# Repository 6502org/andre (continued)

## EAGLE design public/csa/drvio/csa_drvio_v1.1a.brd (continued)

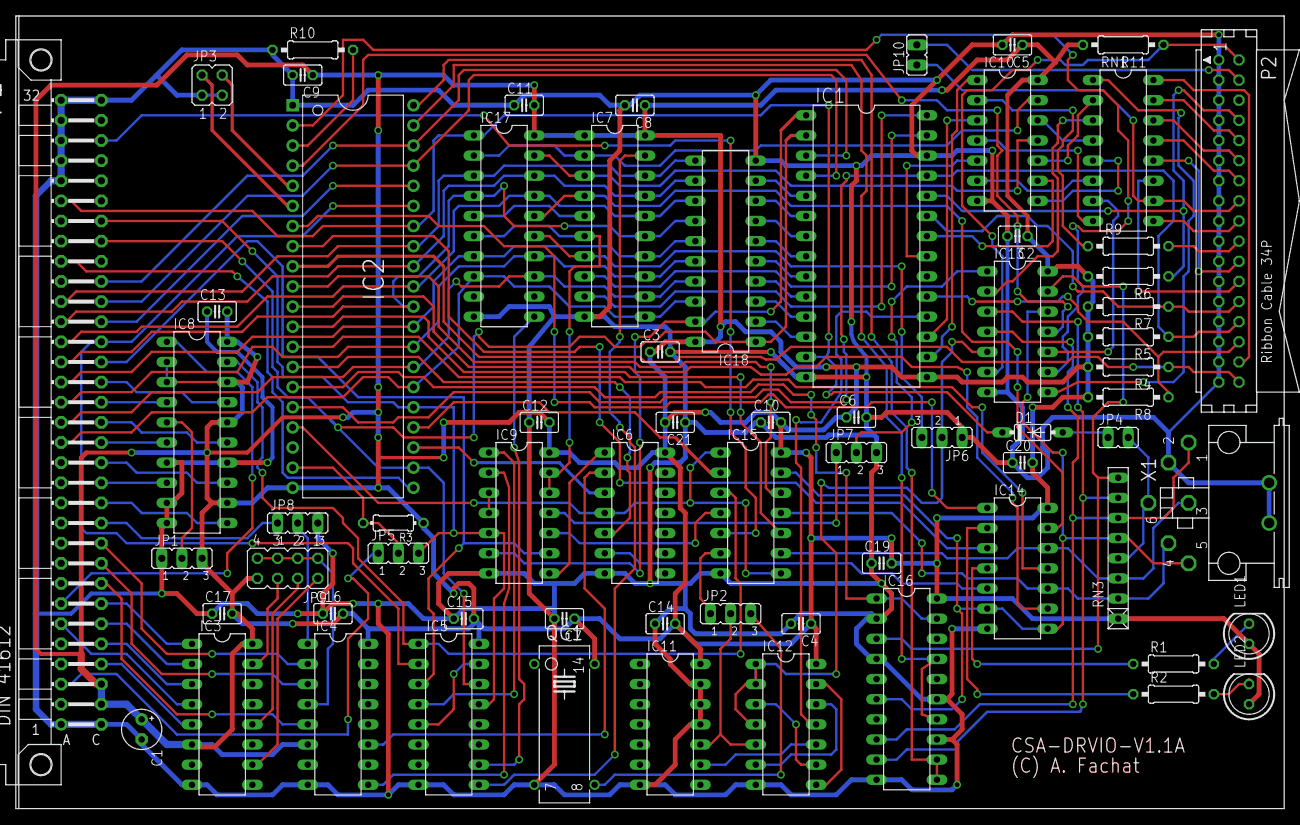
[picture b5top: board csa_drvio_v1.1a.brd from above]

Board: 2 copper layers, 160.0 x 100.0 mm, 68 parts (0 on the bottom side), 143 nets.

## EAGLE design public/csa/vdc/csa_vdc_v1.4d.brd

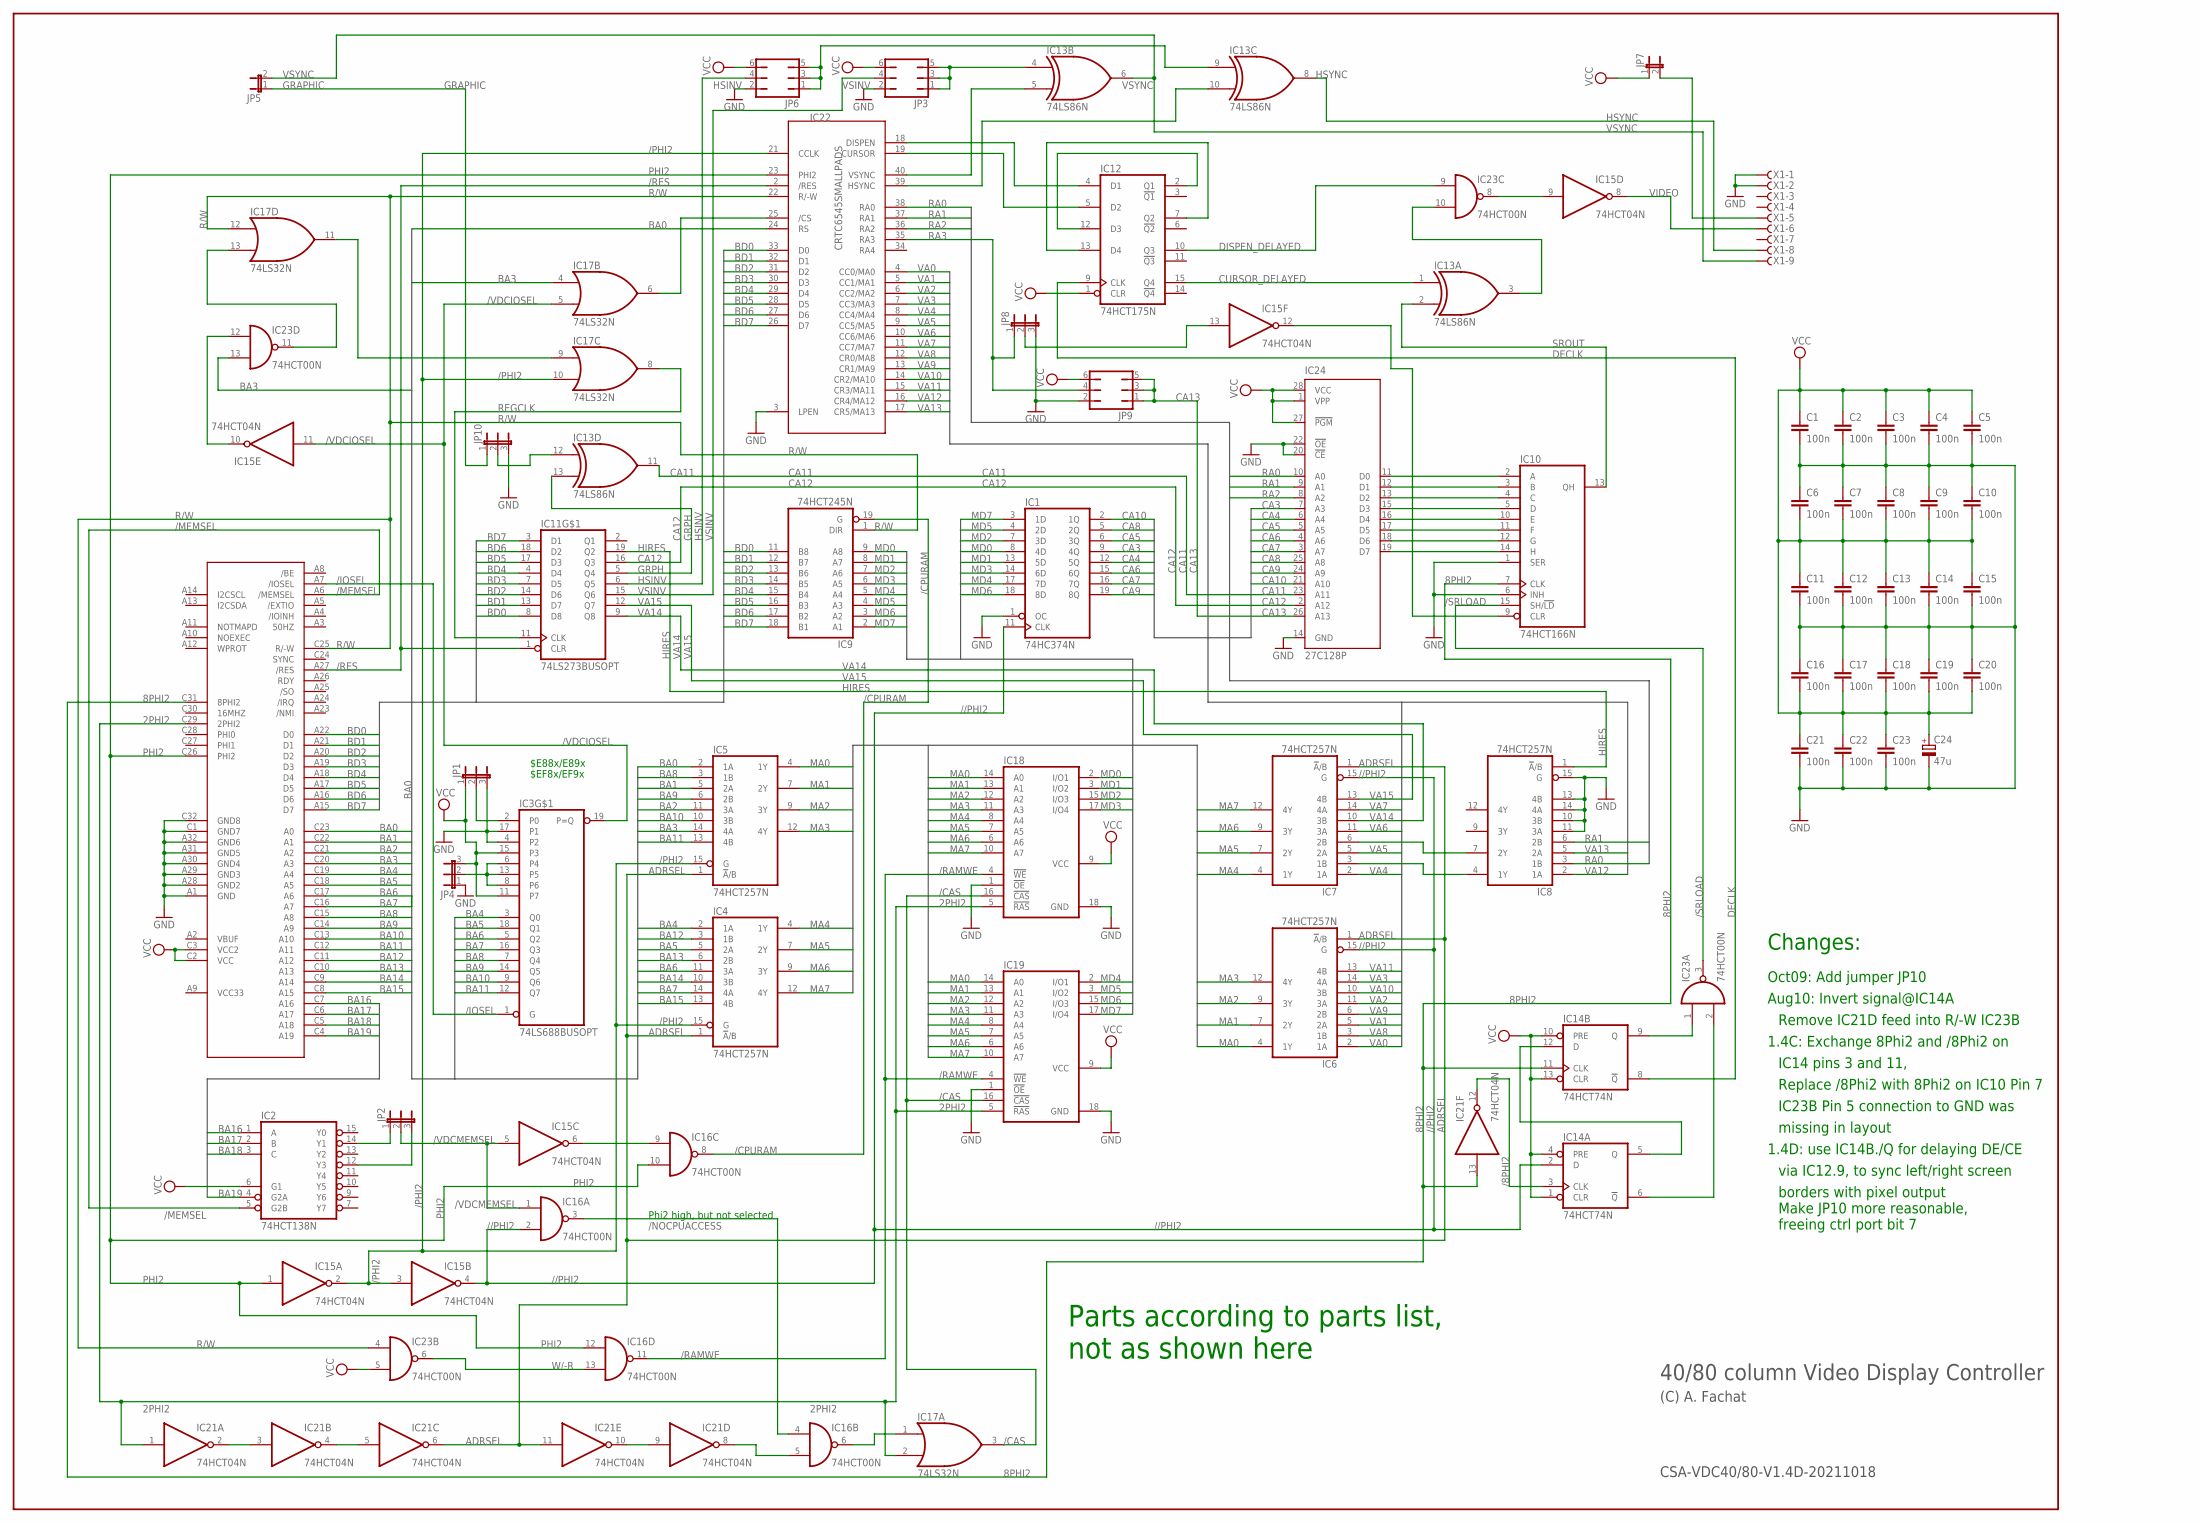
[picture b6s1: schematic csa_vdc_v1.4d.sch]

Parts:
C1, C2, C3, C4, C5, C6, C7, C8, C9, C10, C11, C12, C13, C14, C15, C16, C17, C18, C19, C20, C21, C22, C23: 100n; C025-025X050
C24: 47u; E2,5-5
IC1: 74HC374N; DIL20
IC2: 74HCT138N; DIL16
IC3: 74LS688BUSOPT; DIL20
IC4, IC5, IC6, IC7, IC8: 74HCT257N; DIL16
IC9: 74HCT245N; DIL20
IC10: 74HCT166N; DIL16
IC11: 74LS273BUSOPT; DIL20
IC12: 74HCT175N; DIL16
IC13: 74LS86N; DIL14
IC14: 74HCT74N; DIL14
IC15, IC21: 74HCT04N; DIL14
IC16, IC23: 74HCT00N; DIL14
IC17: 74LS32N; DIL14
IC18, IC19: 41464C; DIL18
IC22: CRTC6545SMALLPADS; DIP40
IC24: 27C128P; DIL28-6
JP1, JP2, JP4, JP8, JP10: JP2E; JP2
JP3, JP6, JP9: JP3Q
JP5, JP7: JP1E; JP1
U$1: CSABUS
X1: F09HPS; F09HP

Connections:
2PHI2: IC17.2 (I1), IC18.5 (!RAS), IC19.5 (!RAS), IC21.1 (I), U$1.C29 (2PHI2)
8PHI2: IC10.7 (CLK), IC14.11 (CLK), IC21.13 (I), U$1.C31 (8PHI2)
/8PHI2: IC14.3 (CLK), IC21.12 (O)
//PHI2: IC1.11 (CLK), IC6.15 (G), IC7.15 (G), IC14.2 (D), IC15.4 (O), IC16.2 (I1)
/CAS: IC17.3 (O), IC18.16 (!CAS), IC19.16 (!CAS)
/CPURAM: IC9.19 (G), IC16.8 (O)
/IOSEL: IC3.1 (G), U$1.A7 (/IOSEL)
/MEMSEL: IC2.5 (G2B), U$1.A6 (/MEMSEL)
/NOCPUACCESS: IC16.3 (O), IC16.4 (I0)
/PHI2: IC4.15 (G), IC5.15 (G), IC15.2 (O), IC15.3 (I), IC17.10 (I1), IC22.21 (CCLK)
/RAMWE: IC16.11 (O), IC18.4 (!WE), IC19.4 (!WE)
/RES: IC11.1 (CLR), IC22.2 (/RES), U$1.A27 (/RES)
/SRLOAD: IC10.15 (SH/!LD), IC23.3 (O)
/VDCIOSEL: IC3.19 (P=Q), IC15.11 (I), IC17.5 (I1)
/VDCMEMSEL: IC15.5 (I), IC16.1 (I0), JP2.2
ADRSEL: IC4.1 (!A!/B), IC5.1 (!A!/B), IC6.1 (!A!/B), IC7.1 (!A!/B), IC21.6 (O), IC21.11 (I)
BA0: IC5.2 (1A), IC22.24 (RS), U$1.C23 (A0)
BA1: IC5.5 (2A), U$1.C22 (A1)
BA2: IC5.11 (3A), U$1.C21 (A2)
BA3: IC5.14 (4A), IC17.4 (I0), IC23.13 (I1), U$1.C20 (A3)
BA4: IC3.3 (Q0), IC4.2 (1A), U$1.C19 (A4)
BA5: IC3.18 (Q1), IC4.5 (2A), U$1.C18 (A5)
BA6: IC3.5 (Q2), IC4.11 (3A), U$1.C17 (A6)
BA7: IC3.16 (Q3), IC4.14 (4A), U$1.C16 (A7)
BA8: IC3.7 (Q4), IC5.3 (1B), U$1.C15 (A8)
BA9: IC3.14 (Q5), IC5.6 (2B), U$1.C14 (A9)
BA10: IC3.9 (Q6), IC5.10 (3B), U$1.C13 (A10)
BA11: IC3.12 (Q7), IC5.13 (4B), U$1.C12 (A11)
BA12: IC4.3 (1B), U$1.C11 (A12)
BA13: IC4.6 (2B), U$1.C10 (A13)
BA14: IC4.10 (3B), U$1.C9 (A14)
BA15: IC4.13 (4B), U$1.C8 (A15)
BA16: IC2.1 (A), U$1.C7 (A16)
BA17: IC2.2 (B), U$1.C6 (A17)
BA18: IC2.3 (C), U$1.C5 (A18)
BA19: IC2.4 (G2A), U$1.C4 (A19)
BD0: IC9.11 (B8), IC11.8 (D8), IC22.33 (D0), U$1.A22 (D0)
BD1: IC9.12 (B7), IC11.13 (D7), IC22.32 (D1), U$1.A21 (D1)
BD2: IC9.13 (B6), IC11.14 (D6), IC22.31 (D2), U$1.A20 (D2)
BD3: IC9.14 (B5), IC11.7 (D5), IC22.30 (D3), U$1.A19 (D3)
BD4: IC9.15 (B4), IC11.4 (D4), IC22.29 (D4), U$1.A18 (D4)
BD5: IC9.16 (B3), IC11.17 (D3), IC22.28 (D5), U$1.A17 (D5)
BD6: IC9.17 (B2), IC11.18 (D2), IC22.27 (D6), U$1.A16 (D6)
BD7: IC9.18 (B1), IC11.3 (D1), IC22.26 (D7), U$1.A15 (D7)
CA3: IC1.9 (4Q), IC24.7 (A3)
CA4: IC1.12 (5Q), IC24.6 (A4)
CA5: IC1.6 (3Q), IC24.5 (A5)
CA6: IC1.15 (6Q), IC24.4 (A6)
CA7: IC1.16 (7Q), IC24.3 (A7)
CA8: IC1.5 (2Q), IC24.25 (A8)
CA9: IC1.19 (8Q), IC24.24 (A9)
CA10: IC1.2 (1Q), IC24.21 (A10)
CA11: IC13.11 (O), IC24.23 (A11)
CA12: IC11.16 (Q3), IC24.2 (A12)
CA13: IC24.26 (A13), JP9.1, JP9.3, JP9.5
CURSOR_DELAYED: IC12.15 (Q4), IC13.1 (I0)
DECLK: IC12.9 (CLK), IC14.8 (!Q)
DISPEN_DELAYED: IC12.10 (Q3), IC23.9 (I0)
GND: C1.2, C2.2, C3.2, C4.2, C5.2, C6.1, C7.1, C8.1, C9.1, C10.1, C11.2, C12.2, C13.2, C14.2, C15.2, C16.1, C17.1, C18.1, C19.1, C20.1, C21.2, C22.2, C23.2, C24.-, IC1.1 (OC), IC1.10 (GND), IC2.8 (GND), IC3.4 (P2), IC3.10 (GND), IC3.17 (P1), IC4.8 (GND), IC5.8 (GND), IC6.8 (GND), IC7.8 (GND), IC8.8 (GND), IC8.10 (3B), IC8.11 (3A), IC8.13 (4B), IC8.14 (4A), IC8.15 (G), IC9.10 (GND), IC10.1 (SER), IC10.6 (INH), IC10.8 (GND), IC11.10 (GND), IC12.8 (GND), IC13.7 (GND), IC14.7 (GND), IC15.7 (GND), IC16.7 (GND), IC17.7 (GND), IC18.1 (!OE), IC18.18 (GND), IC19.1 (!OE), IC19.18 (GND), IC21.7 (GND), IC22.1 (GND), IC22.3 (LPEN), IC23.7 (GND), IC24.14 (GND), IC24.20 (!CE), IC24.22 (!OE), JP1.3, JP3.2, JP4.1, JP6.2, JP8.3, JP9.2, JP10.3, U$1.A1 (GND), U$1.A28 (GND2), U$1.A29 (GND3), U$1.A30 (GND4), U$1.A31 (GND5), U$1.A32 (GND6), U$1.C1 (GND7), U$1.C32 (GND8), X1.1, X1.2
GRAPHIC: JP5.1, JP10.1
GRPH: IC11.5 (Q4), IC13.13 (I1)
HIRES: IC8.1 (!A!/B), IC11.19 (Q2)
HSINV: IC11.6 (Q5), JP6.4
HSYNC: IC13.8 (O), X1.8
MA0: IC5.4 (1Y), IC6.4 (1Y), IC18.14 (A0), IC19.14 (A0)
MA1: IC5.7 (2Y), IC6.7 (2Y), IC18.13 (A1), IC19.13 (A1)
MA2: IC5.9 (3Y), IC6.9 (3Y), IC18.12 (A2), IC19.12 (A2)
MA3: IC5.12 (4Y), IC6.12 (4Y), IC18.11 (A3), IC19.11 (A3)
MA4: IC4.4 (1Y), IC7.4 (1Y), IC18.8 (A4), IC19.8 (A4)
MA5: IC4.7 (2Y), IC7.7 (2Y), IC18.7 (A5), IC19.7 (A5)
MA6: IC4.9 (3Y), IC7.9 (3Y), IC18.6 (A6), IC19.6 (A6)
MA7: IC4.12 (4Y), IC7.12 (4Y), IC18.10 (A7), IC19.10 (A7)
MD0: IC1.8 (4D), IC9.9 (A8), IC18.2 (I/O1)
MD1: IC1.13 (5D), IC9.8 (A7), IC18.3 (I/O2)
MD2: IC1.7 (3D), IC9.7 (A6), IC18.15 (I/O3)
MD3: IC1.14 (6D), IC9.6 (A5), IC18.17 (I/O4)
MD4: IC1.17 (7D), IC9.5 (A4), IC19.2 (I/O1)
MD5: IC1.4 (2D), IC9.4 (A3), IC19.3 (I/O2)
MD6: IC1.18 (8D), IC9.3 (A2), IC19.15 (I/O3)
MD7: IC1.3 (1D), IC9.2 (A1), IC19.17 (I/O4)
unnamed: IC7.3 (1B), IC8.4 (1Y)
unnamed: IC3.2 (P0), JP1.2
unnamed: IC7.6 (2B), IC8.7 (2Y)
unnamed: IC10.2 (A), IC24.11 (D0)
unnamed: IC10.3 (B), IC24.12 (D1)
unnamed: IC10.4 (C), IC24.13 (D2)
unnamed: IC10.5 (D), IC24.15 (D3)
unnamed: IC10.10 (E), IC24.16 (D4)
unnamed: IC10.11 (F), IC24.17 (D5)
unnamed: IC10.12 (G), IC24.18 (D6)
unnamed: IC10.14 (H), IC24.19 (D7)
unnamed: IC2.14 (Y1), JP2.1
unnamed: IC2.12 (Y3), JP2.3
unnamed: IC14.6 (!Q), IC23.2 (I1)
unnamed: IC12.4 (D1), IC22.18 (DISPEN)
unnamed: IC3.6 (P4), IC3.8 (P6), IC3.13 (P5), JP4.2
unnamed: IC21.2 (O), IC21.3 (I)
unnamed: IC21.4 (O), IC21.5 (I)
unnamed: IC12.5 (D2), IC22.19 (CURSOR)
unnamed: IC21.9 (I), IC21.10 (O)
unnamed: IC13.9 (I0), JP6.1, JP6.3, JP6.5
unnamed: IC16.5 (I1), IC21.8 (O)
unnamed: IC16.6 (O), IC17.1 (I0)
unnamed: IC17.13 (I1), IC23.11 (O)
unnamed: IC15.6 (O), IC16.9 (I0)
unnamed: IC12.2 (Q1), IC12.12 (D3)
unnamed: IC12.7 (Q2), IC12.13 (D4)
unnamed: IC13.4 (I0), JP3.1, JP3.3, JP3.5
unnamed: IC10.9 (CLR), IC15.12 (O)
unnamed: IC13.3 (O), IC23.10 (I1)
unnamed: JP7.2, X1.5
unnamed: IC15.9 (I), IC23.8 (O)
unnamed: IC14.5 (Q), IC14.12 (D)
unnamed: IC13.5 (I1), IC22.40 (VSYNC)
unnamed: IC15.13 (I), JP8.2
unnamed: IC14.9 (Q), IC23.1 (I0)
unnamed: IC13.10 (I1), IC22.39 (HSYNC)
unnamed: IC13.12 (I0), JP10.2
unnamed: IC17.6 (O), IC22.25 (/CS)
unnamed: IC15.10 (O), IC23.12 (I0)
unnamed: IC17.9 (I0), IC17.11 (O)
PHI2: IC15.1 (I), IC16.10 (I1), IC16.12 (I0), IC22.23 (PHI2), U$1.C26 (PHI2)
R/W: IC9.1 (DIR), IC17.12 (I0), IC22.22 (R/-W), IC23.4 (I0), U$1.C25 (R/-W)
RA0: IC8.3 (1B), IC22.38 (RA0), IC24.10 (A0)
RA1: IC8.6 (2B), IC22.37 (RA1), IC24.9 (A1)
RA2: IC22.36 (RA2), IC24.8 (A2)
RA3: IC22.35 (RA3), JP8.1, JP9.4
REGCLK: IC11.11 (CLK), IC17.8 (O)
SROUT: IC10.13 (QH), IC13.2 (I1)
VA0: IC6.2 (1A), IC22.4 (CC0/MA0)
VA1: IC6.5 (2A), IC22.5 (CC1/MA1)
VA2: IC6.11 (3A), IC22.6 (CC2/MA2)
VA3: IC6.14 (4A), IC22.7 (CC3/MA3)
VA4: IC7.2 (1A), IC22.8 (CC4/MA4)
VA5: IC7.5 (2A), IC22.9 (CC5/MA5)
VA6: IC7.11 (3A), IC22.10 (CC6/MA6)
VA7: IC7.14 (4A), IC22.11 (CC7/MA7)
VA8: IC6.3 (1B), IC22.12 (CR0/MA8)
VA9: IC6.6 (2B), IC22.13 (CR1/MA9)
VA10: IC6.10 (3B), IC22.14 (CR2/MA10)
VA11: IC6.13 (4B), IC22.15 (CR3/MA11)
VA12: IC8.2 (1A), IC22.16 (CR4/MA12)
VA13: IC8.5 (2A), IC22.17 (CR5/MA13)
VA14: IC7.10 (3B), IC11.9 (Q8)
VA15: IC7.13 (4B), IC11.12 (Q7)
VCC: C1.1, C2.1, C3.1, C4.1, C5.1, C6.2, C7.2, C8.2, C9.2, C10.2, C11.1, C12.1, C13.1, C14.1, C15.1, C16.2, C17.2, C18.2, C19.2, C20.2, C21.1, C22.1, C23.1, C24.+, IC1.20 (VCC), IC2.6 (G1), IC2.16 (VCC), IC3.11 (P7), IC3.15 (P3), IC3.20 (VCC), IC4.16 (VCC), IC5.16 (VCC), IC6.16 (VCC), IC7.16 (VCC), IC8.16 (VCC), IC9.20 (VCC), IC10.16 (VCC), IC11.20 (VCC), IC12.1 (CLR), IC12.16 (VCC), IC13.14 (VCC), IC14.1 (CLR), IC14.4 (PRE), IC14.10 (PRE), IC14.13 (CLR), IC14.14 (VCC), IC15.14 (VCC), IC16.14 (VCC), IC17.14 (VCC), IC18.9 (VCC), IC19.9 (VCC), IC21.14 (VCC), IC22.20 (VCC), IC23.5 (I1), IC23.14 (VCC), IC24.1 (VPP), IC24.27 (!PGM), IC24.28 (VCC), JP1.1, JP3.6, JP4.3, JP6.6, JP7.1, JP9.6, U$1.C2 (VCC), U$1.C3 (VCC2)
VIDEO: IC15.8 (O), X1.6
VSINV: IC11.15 (Q6), JP3.4
VSYNC: IC13.6 (O), JP5.2, X1.9
W/-R: IC16.13 (I1), IC23.6 (O)

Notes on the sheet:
40/80 column Video Display Controller
CSA-VDC40/80-V1.4D-20211018
(C) A. Fachat
Phi2 high, but not selected
$E88x/E89x
$EF8x/EF9x
Parts according to parts list,
not as shown here
Changes:
Oct09: Add jumper JP10
Aug10: Invert signal@IC14A
Remove IC21D feed into R/-W IC23B
1.4C: Exchange 8Phi2 and /8Phi2 on
Replace /8Phi2 with 8Phi2 on IC10 Pin 7
IC14 pins 3 and 11,
IC23B Pin 5 connection to GND was
missing in layout
1.4D: use IC14B./Q for delaying DE/CE
via IC12.9, to sync left/right screen
borders with pixel output
Make JP10 more reasonable, freeing ctrl port bit 7

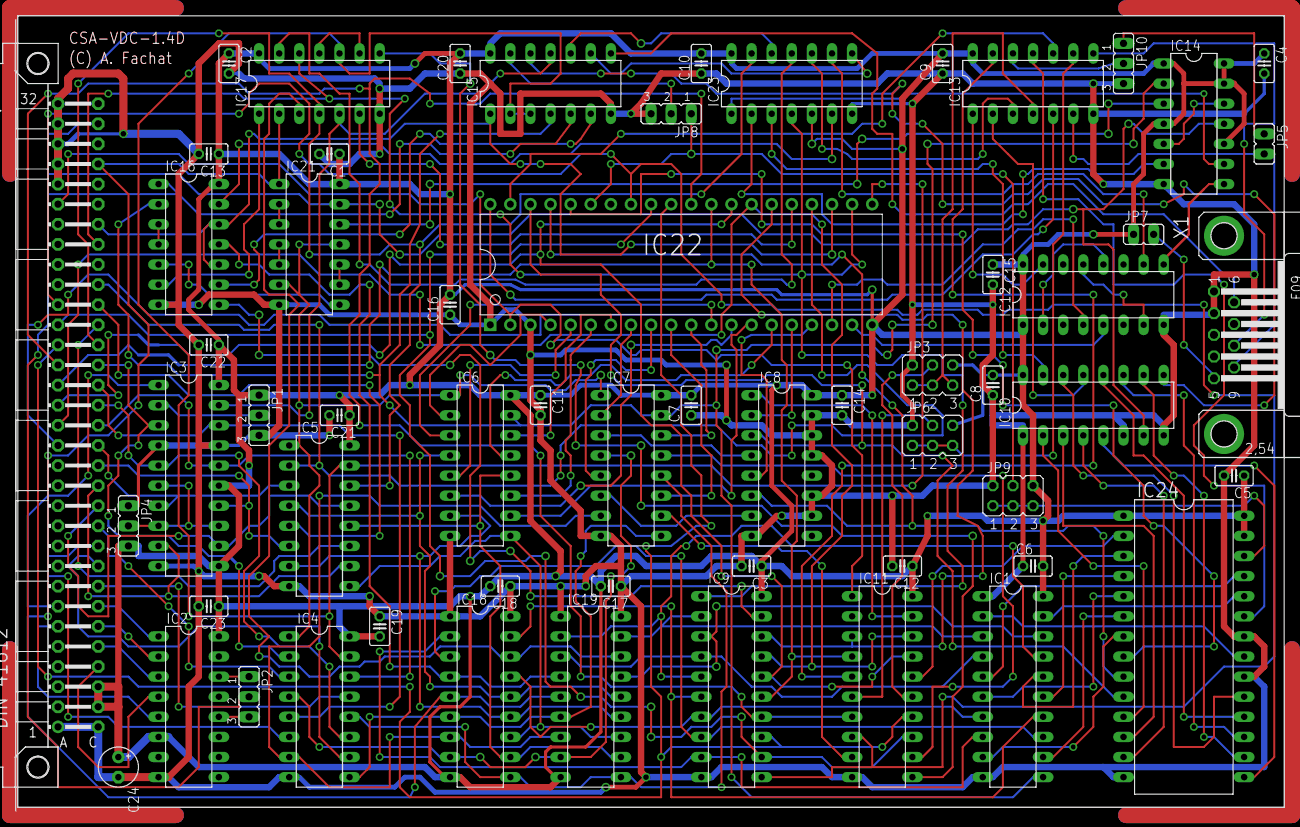
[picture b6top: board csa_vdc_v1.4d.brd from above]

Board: 2 copper layers, 160.0 x 100.0 mm, 59 parts (0 on the bottom side), 150 nets.

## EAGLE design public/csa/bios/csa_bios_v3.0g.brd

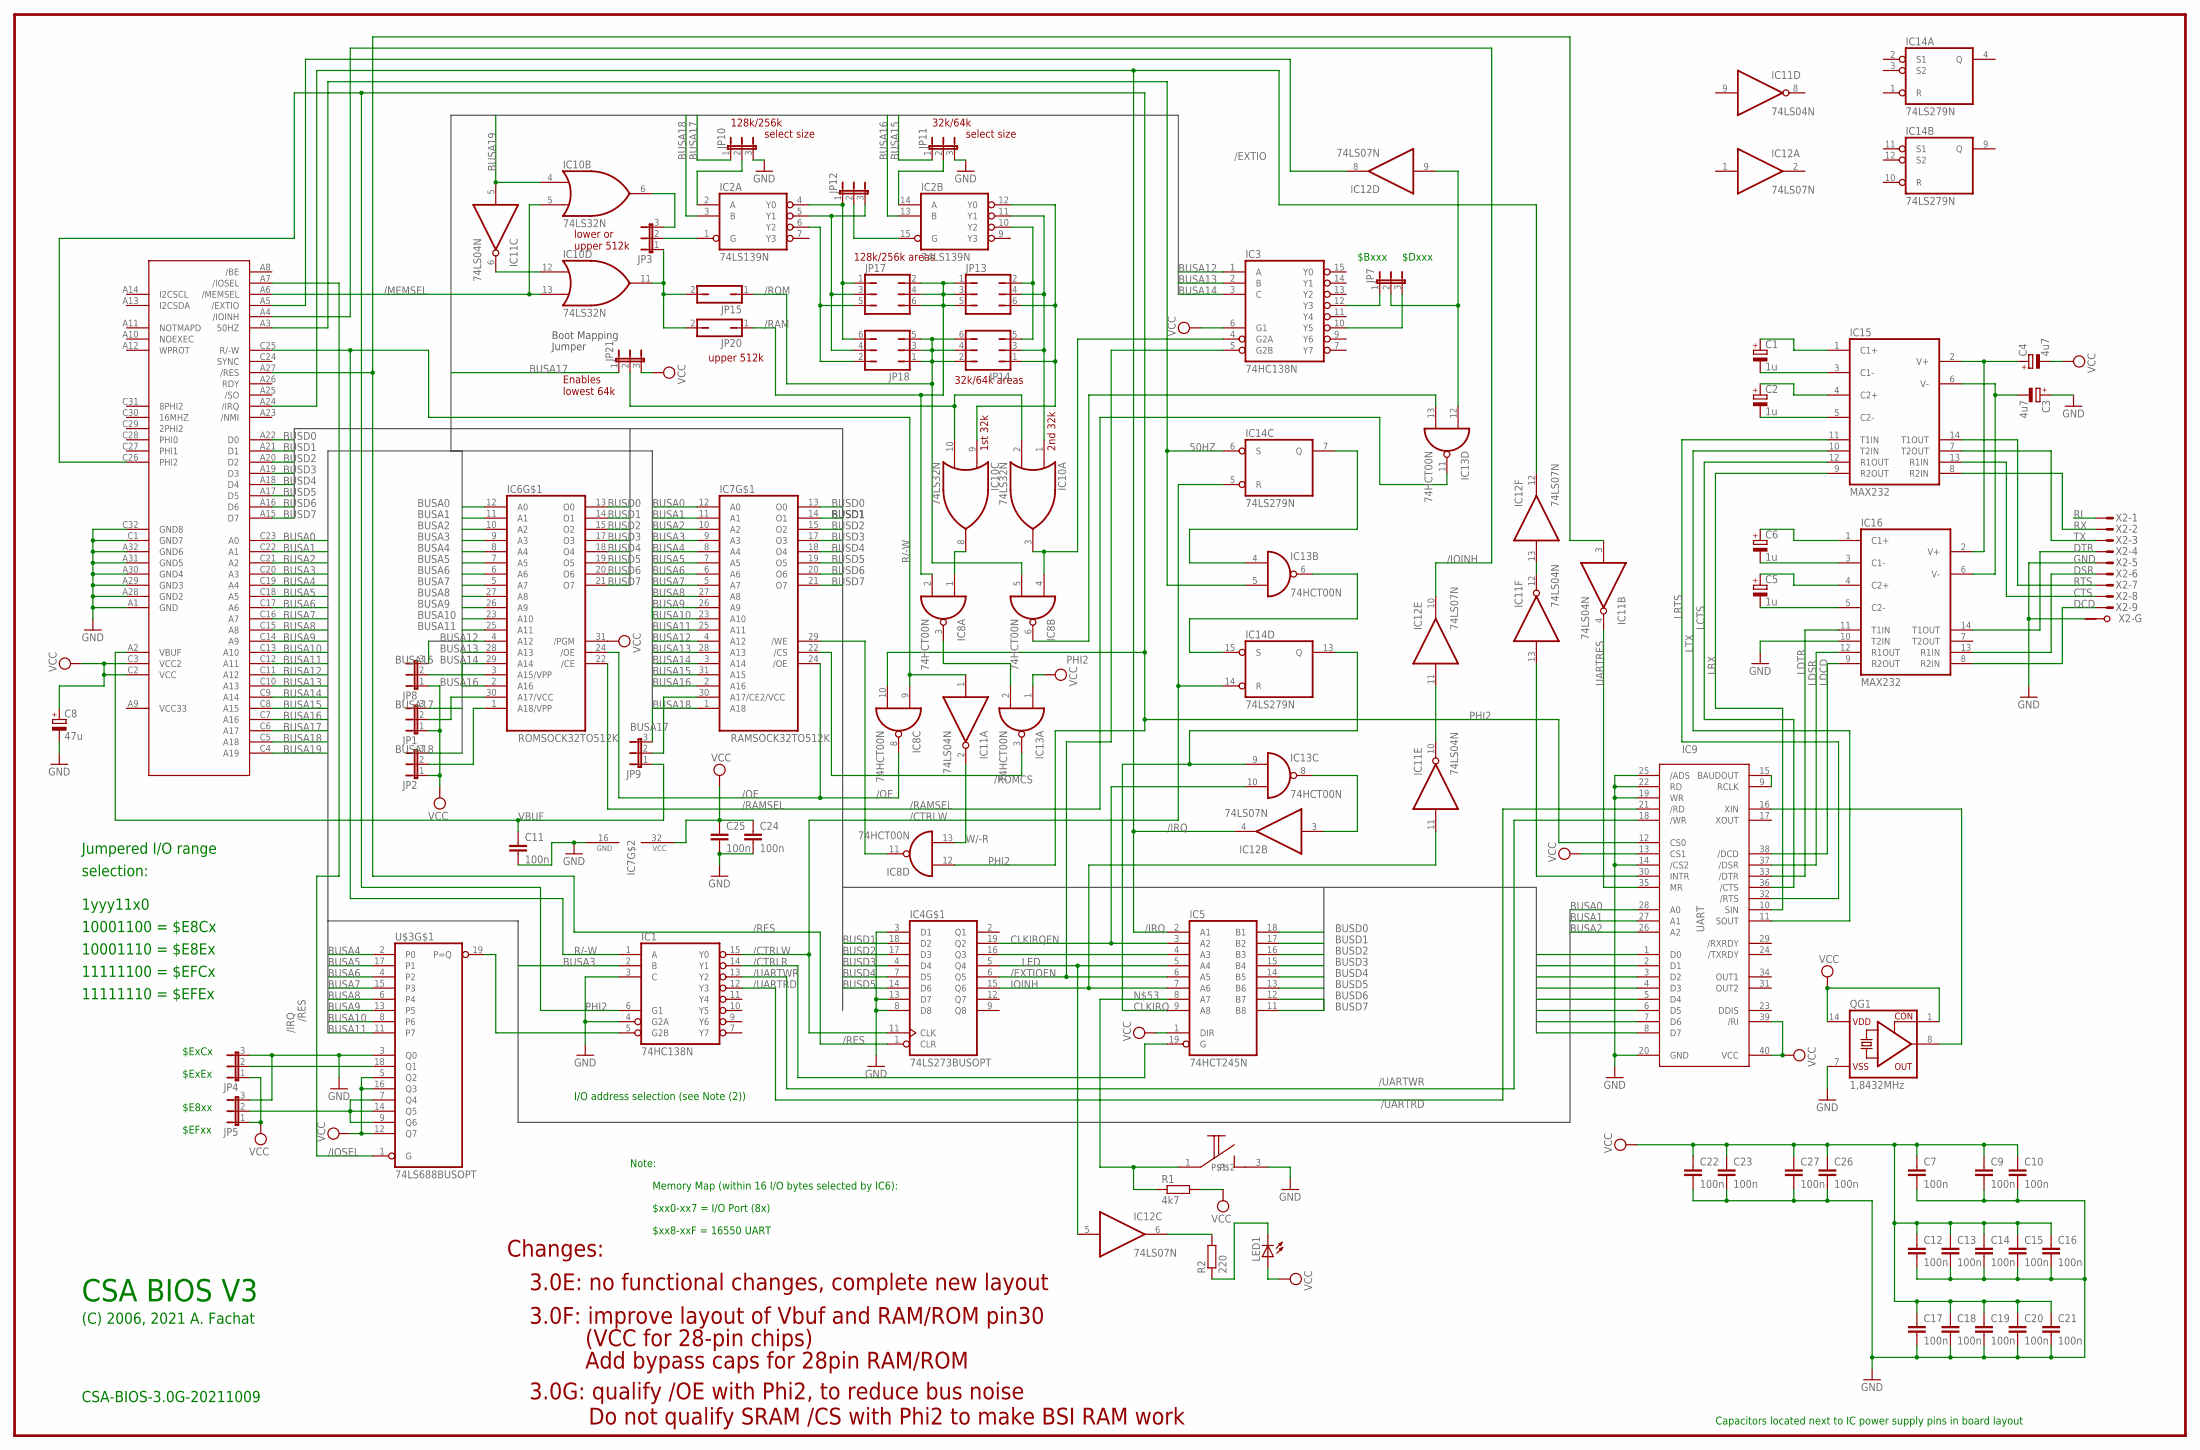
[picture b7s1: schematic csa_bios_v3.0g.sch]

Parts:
C1, C2, C5, C6: 1u; E2,5-6
C3, C4: 4u7; E2,5-6
C7, C9, C10, C11, C12, C13, C14, C15, C16, C17, C18, C19, C20, C21, C22, C23, C24, C25, C26, C27: 100n; C025-025X050
C8: 47u; E2,5-7
IC1, IC3: 74HC138N; DIL16
IC2: 74LS139N; DIL16
IC4: 74LS273BUSOPT; DIL20
IC5: 74HCT245N; DIL20
IC6: ROMSOCK32TO512K; DIL32OPT28
IC7: RAMSOCK32TO512K; DIL32OPT28
IC8, IC13: 74HCT00N; DIL14
IC9: UART; DIL40
IC10: 74LS32N; DIL14
IC11: 74LS04N; DIL14
IC12: 74LS07N; DIL14
IC14: 74LS279N; DIL16
IC15, IC16: MAX232; DIL16
JP1, JP2, JP3, JP4, JP5, JP7, JP8, JP9, JP10, JP11, JP12, JP21: JP2E; JP2
JP13, JP14, JP17, JP18: JP3Q
JP15, JP20: JP1Q; JP1
LED1: LED5MM
QG1: 1,8432MHz; SG51
R1: 4k7; 0204/7
R2: 220; 0207/10
U$1: CSABUS
U$2: TASTER
U$3: 74LS688BUSOPT; DIL20
X2: M09HPS; M09HP

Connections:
50HZ: IC13.5 (I1), IC14.6 (S), U$1.A3 (50HZ)
/CTRLR: IC1.14 (Y1), IC5.19 (G)
/CTRLW: IC1.15 (Y0), IC4.11 (CLK), IC14.5 (R), IC14.14 (R)
/EXTIO: IC12.8 (O), U$1.A5 (/EXTIO)
/EXTIOEN: IC3.5 (G2B), IC4.6 (Q5), IC5.6 (A5)
/IOINH: IC12.10 (O), U$1.A4 (/IOINH)
/IOSEL: U$1.A7 (/IOSEL), U$3.1 (G)
/IRQ: IC5.2 (A1), IC12.4 (O), IC12.12 (O), U$1.A24 (/IRQ)
/MEMSEL: IC10.5 (I1), IC10.13 (I1), U$1.A6 (/MEMSEL)
/OE: IC6.24 (/OE), IC7.24 (/OE), IC8.8 (O)
/RAM: IC8.2 (I1), JP13.1, JP13.3, JP13.5, JP17.2, JP17.4, JP17.6, JP20.1
/RAMSEL: IC6.22 (/CE), IC13.11 (O)
/RES: IC4.1 (CLR), IC11.3 (I), U$1.A27 (/RES)
/ROM: IC8.5 (I1), JP14.2, JP14.4, JP14.6, JP15.1, JP18.1, JP18.3, JP18.5
/ROMCS: IC7.22 (/CS), IC13.3 (O)
/UARTRD: IC1.12 (Y3), IC9.21 (/RD)
/UARTWR: IC1.13 (Y2), IC9.18 (/WR)
BUSA0: IC6.12 (A0), IC7.12 (A0), IC9.28 (A0), U$1.C23 (A0)
BUSA1: IC6.11 (A1), IC7.11 (A1), IC9.27 (A1), U$1.C22 (A1)
BUSA2: IC6.10 (A2), IC7.10 (A2), IC9.26 (A2), U$1.C21 (A2)
BUSA3: IC1.2 (B), IC6.9 (A3), IC7.9 (A3), U$1.C20 (A3)
BUSA4: IC6.8 (A4), IC7.8 (A4), U$1.C19 (A4), U$3.2 (P0)
BUSA5: IC6.7 (A5), IC7.7 (A5), U$1.C18 (A5), U$3.17 (P1)
BUSA6: IC6.6 (A6), IC7.6 (A6), U$1.C17 (A6), U$3.4 (P2)
BUSA7: IC6.5 (A7), IC7.5 (A7), U$1.C16 (A7), U$3.15 (P3)
BUSA8: IC6.27 (A8), IC7.27 (A8), U$1.C15 (A8), U$3.6 (P4)
BUSA9: IC6.26 (A9), IC7.26 (A9), U$1.C14 (A9), U$3.13 (P5)
BUSA10: IC6.23 (A10), IC7.23 (A10), U$1.C13 (A10), U$3.8 (P6)
BUSA11: IC6.25 (A11), IC7.25 (A11), U$1.C12 (A11), U$3.11 (P7)
BUSA12: IC3.1 (A), IC6.4 (A12), IC7.4 (A12), U$1.C11 (A12)
BUSA13: IC3.2 (B), IC6.28 (A13), IC7.28 (A13), U$1.C10 (A13)
BUSA14: IC3.3 (C), IC6.29 (A14), IC7.3 (A14), U$1.C9 (A14)
BUSA15: IC7.31 (A15), JP8.3, JP11.1, U$1.C8 (A15)
BUSA16: IC2.13 (B), IC6.2 (A16), IC7.2 (A16), U$1.C7 (A16)
BUSA17: JP1.3, JP9.3, JP10.1, JP21.1, U$1.C6 (A17)
BUSA17X: IC10.2 (I1), IC10.10 (I1), JP21.2
BUSA18: IC2.3 (B), IC7.1 (A18), JP2.3, U$1.C5 (A18)
BUSA19: IC10.4 (I0), IC11.5 (I), U$1.C4 (A19)
BUSD0: IC5.18 (B1), IC6.13 (O0), IC7.13 (O0), IC9.1 (D0), U$1.A22 (D0)
BUSD1: IC4.18 (D2), IC5.17 (B2), IC6.14 (O1), IC7.14 (O1), IC9.2 (D1), U$1.A21 (D1)
BUSD2: IC4.17 (D3), IC5.16 (B3), IC6.15 (O2), IC7.15 (O2), IC9.3 (D2), U$1.A20 (D2)
BUSD3: IC4.4 (D4), IC5.15 (B4), IC6.17 (O3), IC7.17 (O3), IC9.4 (D3), U$1.A19 (D3)
BUSD4: IC4.7 (D5), IC5.14 (B5), IC6.18 (O4), IC7.18 (O4), IC9.5 (D4), U$1.A18 (D4)
BUSD5: IC4.14 (D6), IC5.13 (B6), IC6.19 (O5), IC7.19 (O5), IC9.6 (D5), U$1.A17 (D5)
BUSD6: IC5.12 (B7), IC6.20 (O6), IC7.20 (O6), IC9.7 (D6), U$1.A16 (D6)
BUSD7: IC5.11 (B8), IC6.21 (O7), IC7.21 (O7), IC9.8 (D7), U$1.A15 (D7)
CLKIRQ: IC5.9 (A8), IC13.9 (I0), IC14.13 (Q)
CLKIRQEN: IC4.19 (Q2), IC5.3 (A2), IC13.10 (I1)
CTS: IC15.13 (R1IN), X2.8 (M)
DCD: IC16.8 (R2IN), X2.9 (M)
DSR: IC16.13 (R1IN), X2.6 (M)
DTR: IC16.14 (T1OUT), X2.4 (M)
GND: C3.+, C7.2, C8.-, C9.2, C10.2, C11.2, C12.2, C13.2, C14.2, C15.2, C16.2, C17.2, C18.2, C19.2, C20.2, C21.2, C22.2, C23.2, C24.2, C25.2, C26.2, C27.2, IC1.3 (C), IC1.4 (G2A), IC1.8 (GND), IC2.8 (GND), IC3.8 (GND), IC4.3 (D1), IC4.8 (D8), IC4.10 (GND), IC4.13 (D7), IC5.10 (GND), IC6.16 (GND), IC7.16 (GND), IC8.7 (GND), IC9.14 (/CS2), IC9.19 (WR), IC9.20 (GND), IC9.22 (RD), IC9.25 (/ADS), IC10.7 (GND), IC11.7 (GND), IC12.7 (GND), IC13.7 (GND), IC14.8 (GND), IC15.15 (GND), IC16.10 (T2IN), IC16.15 (GND), JP4.3, JP5.3, JP10.3, JP11.3, QG1.7 (VSS), U$1.A1 (GND), U$1.A28 (GND2), U$1.A29 (GND3), U$1.A30 (GND4), U$1.A31 (GND5), U$1.A32 (GND6), U$1.C1 (GND7), U$1.C32 (GND8), U$2.3, U$3.3 (Q0), U$3.10 (GND), X2.5 (M), X2.G1
IOINH: IC4.15 (Q6), IC5.7 (A6), IC11.11 (I)
LCTS: IC9.36 (/CTS), IC15.12 (R1OUT)
LDCD: IC9.38 (/DCD), IC16.9 (R2OUT)
LDSR: IC9.37 (/DSR), IC16.12 (R1OUT)
LDTR: IC9.33 (/DTR), IC16.11 (T1IN)
LED: IC4.5 (Q4), IC5.5 (A4), IC12.5 (I)
LRTS: IC9.32 (/RTS), IC15.11 (T1IN)
LRX: IC9.10 (SIN), IC15.9 (R2OUT)
LTX: IC9.11 (SOUT), IC15.10 (T2IN)
unnamed: IC8.3 (O), IC13.2 (I1)
unnamed: IC6.3 (A15/VPP), JP8.2
unnamed: IC9.9 (RCLK), IC9.15 (BAUDOUT)
unnamed: IC6.30 (A17/VCC), JP1.2
unnamed: IC6.1 (A18/VPP), JP2.2
unnamed: IC1.5 (G2B), U$3.19 (P=Q)
unnamed: IC7.30 (A17/CE2/VCC), JP9.2
unnamed: IC2.6 (Y2), JP17.5, JP18.2
unnamed: IC13.4 (I0), IC14.7 (Q)
unnamed: IC2.10 (Y2), JP13.2, JP14.5
unnamed: IC10.12 (I0), IC11.6 (O)
unnamed: IC10.6 (O), JP3.3
unnamed: IC10.11 (O), JP3.1, JP15.2, JP20.2
unnamed: IC2.1 (G), JP3.2
unnamed: IC4.16 (Q3), IC5.4 (A3)
unnamed: IC2.2 (A), JP10.2
unnamed: IC2.14 (A), JP11.2
unnamed: IC2.4 (Y0), JP12.1, JP17.1, JP18.6
unnamed: IC8.1 (I0), IC10.8 (O)
unnamed: JP4.2, U$3.18 (Q1)
unnamed: IC13.6 (O), IC14.15 (S)
unnamed: IC2.5 (Y1), JP12.3, JP17.3, JP18.4
unnamed: IC2.15 (G), JP12.2
unnamed: IC12.3 (I), IC13.8 (O)
unnamed: IC2.11 (Y1), IC10.1 (I0), JP13.4, JP14.3
unnamed: IC12.6 (O), R2.2
unnamed: LED1.K (C), R2.1
unnamed: IC12.9 (I), IC13.12 (I0), JP7.2
unnamed: IC7.29 (/WE), IC8.11 (O)
unnamed: IC11.10 (O), IC12.11 (I)
unnamed: IC2.12 (Y0), IC10.9 (I0), JP13.6, JP14.1
unnamed: IC8.6 (O), IC13.13 (I1)
unnamed: IC9.16 (XIN), QG1.8 (OUT)
unnamed: IC11.12 (O), IC12.13 (I)
unnamed: C1.-, IC15.3 (C1-)
unnamed: C1.+, IC15.1 (C1+)
unnamed: C6.-, IC16.3 (C1-)
unnamed: C6.+, IC16.1 (C1+)
unnamed: C2.-, IC15.5 (C2-)
unnamed: C2.+, IC15.4 (C2+)
unnamed: C5.-, IC16.5 (C2-)
unnamed: C5.+, IC16.4 (C2+)
unnamed: C3.-, IC15.6 (V-), IC16.6 (V-)
unnamed: C4.+, IC15.2 (V+), IC16.2 (V+)
unnamed: IC5.8 (A7), R1.1, U$2.1
unnamed: IC3.4 (G2A), IC8.4 (I0), IC10.3 (O)
unnamed: JP5.2, U$3.7 (Q4), U$3.9 (Q6), U$3.14 (Q5)
unnamed: IC3.12 (Y3), JP7.1
unnamed: IC3.10 (Y5), JP7.3
PHI2: IC1.6 (G1), IC8.10 (I1), IC8.12 (I0), IC9.12 (CS0), U$1.C26 (PHI2)
R/-W: IC1.1 (A), IC8.9 (I0), IC11.1 (I), U$1.C25 (R/-W)
RI: X2.1 (M)
RTS: IC15.14 (T1OUT), X2.7 (M)
RX: IC15.8 (R2IN), X2.2 (M)
TX: IC15.7 (T2OUT), X2.3 (M)
UARTINT: IC9.30 (INTR), IC11.13 (I)
UARTRES: IC9.35 (MR), IC11.4 (O)
VBUF: C11.1, JP9.1, U$1.A2 (VBUF)
VCC: C4.-, C7.1, C8.+, C9.1, C10.1, C12.1, C13.1, C14.1, C15.1, C16.1, C17.1, C18.1, C19.1, C20.1, C21.1, C22.1, C23.1, C24.1, C25.1, C26.1, C27.1, IC1.16 (VCC), IC2.16 (VCC), IC3.6 (G1), IC3.16 (VCC), IC4.20 (VCC), IC5.1 (DIR), IC5.20 (VCC), IC6.31 (/PGM), IC6.32 (VCC), IC7.32 (VCC), IC8.14 (VCC), IC9.13 (CS1), IC9.39 (/RI), IC9.40 (VCC), IC10.14 (VCC), IC11.14 (VCC), IC12.14 (VCC), IC13.1 (I0), IC13.14 (VCC), IC14.16 (VCC), IC15.16 (VCC), IC16.16 (VCC), JP1.1, JP2.1, JP4.1, JP5.1, JP8.1, JP21.3, LED1.A, QG1.1 (CON), QG1.14 (VDD), R1.2, U$1.C2 (VCC), U$1.C3 (VCC2), U$3.5 (Q2), U$3.12 (Q7), U$3.16 (Q3), U$3.20 (VCC)
W/-R: IC8.13 (I1), IC11.2 (O)

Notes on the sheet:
CSA BIOS V3
CSA-BIOS-3.0G-20211009
$ExEx
$ExCx
$EFxx
$E8xx
$Bxxx
$Dxxx
1yyy11x0
10001100 = $E8Cx
10001110 = $E8Ex
11111100 = $EFCx
11111110 = $EFEx
Memory Map (within 16 I/O bytes selected by IC6):
$xx0-xx7 = I/O Port (8x)
$xx8-xxF = 16550 UART
Jumpered I/O range
selection:
Note:
I/O address selection (see Note (2))
Capacitors located next to IC power supply pins in board layout
(C) 2006, 2021 A. Fachat
Boot Mapping
Jumper
Changes:
3.0E: no functional changes, complete new layout
3.0F: improve layout of Vbuf and RAM/ROM pin30
(VCC for 28-pin chips)
Add bypass caps for 28pin RAM/ROM
3.0G: qualify /OE with Phi2, to reduce bus noise Do not qualify SRAM /CS with Phi2 to make BSI RAM work
32k/64k
upper 512k
32k/64k areas
128k/256k areas
128k/256k
select size
lower or upper 512k
1st 32k
2nd 32k
Enables lowest 64k

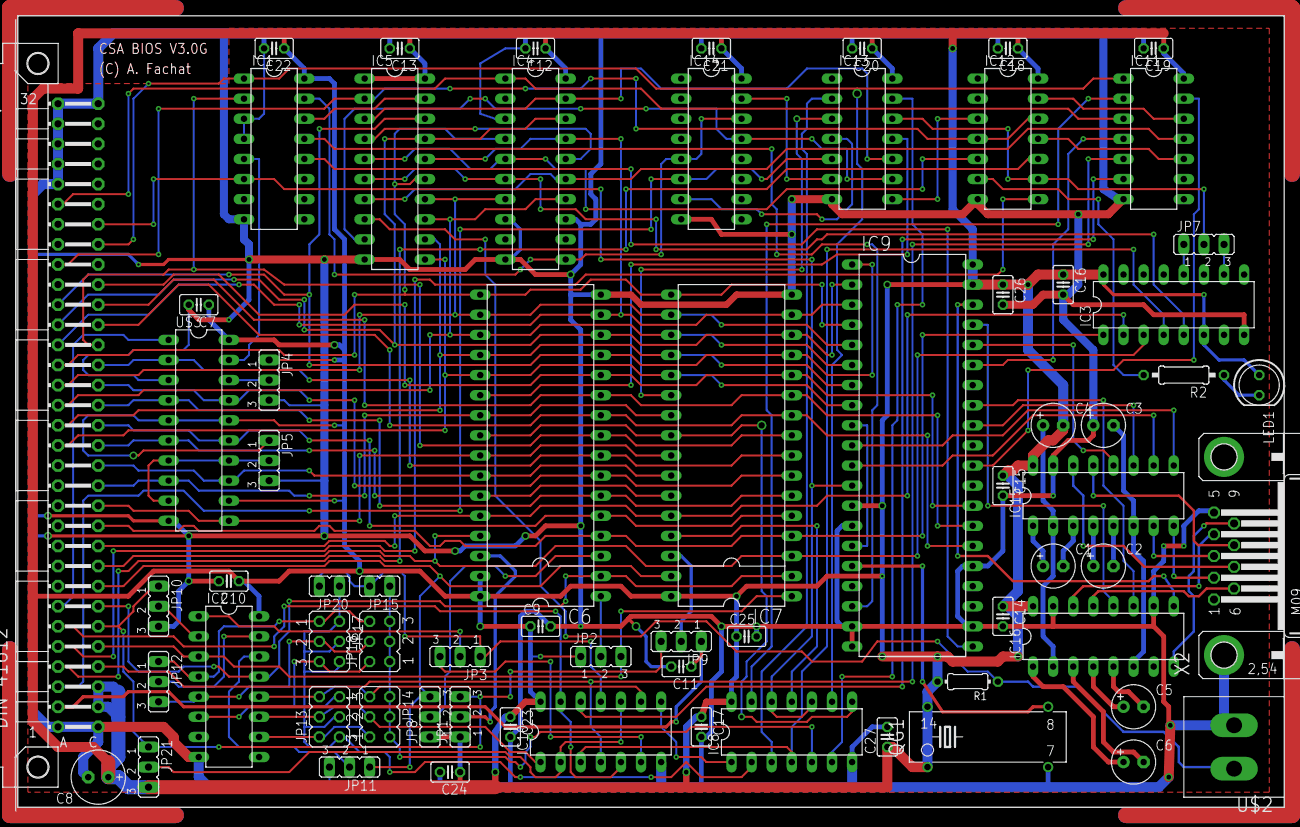
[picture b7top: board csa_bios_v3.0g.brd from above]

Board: 2 copper layers, 160.0 x 100.0 mm, 69 parts (0 on the bottom side), 121 nets.

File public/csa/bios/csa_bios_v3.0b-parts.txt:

Partlist

Part     Value 

C1       1u 
C2       1u 
C3       4u7
C4       4u7 
C5       1u  
C6       1u  
C7       100n
C8       47u 
C9       100n
C10      100n
C12      100n
C13      100n
C14      100n
C15      100n
C16      100n
C17      100n
C18      100n
C19      100n
C20      100n
C21      100n
C22      100n
C23      100n
C25      100n
C26      100n
C27      100n 
IC1      74ALS138
IC2      74ALS139
IC3      74ALS138
IC4      74ALS273
IC5      74ALS245
IC6      ROMSOCK32TO512K 
IC7      RAMSOCK32TO512K 
IC8      74ALS00
IC9      UART 16550A
IC10     74ALS32
IC11     74ALS04
IC12     74LS07
IC13     74ALS00
IC14     74LS279
IC15     MAX232 
IC16     MAX232
LED1     LED5MM  yellow
QG1      1,8432MHz crystal oscillator DIL14E
R1       4k7    
R2       220   
R3       10k 
U$1      CSABUS 
U$2      TASTER  
U$3      74ALS688
X2       9pin D-Sub Male
